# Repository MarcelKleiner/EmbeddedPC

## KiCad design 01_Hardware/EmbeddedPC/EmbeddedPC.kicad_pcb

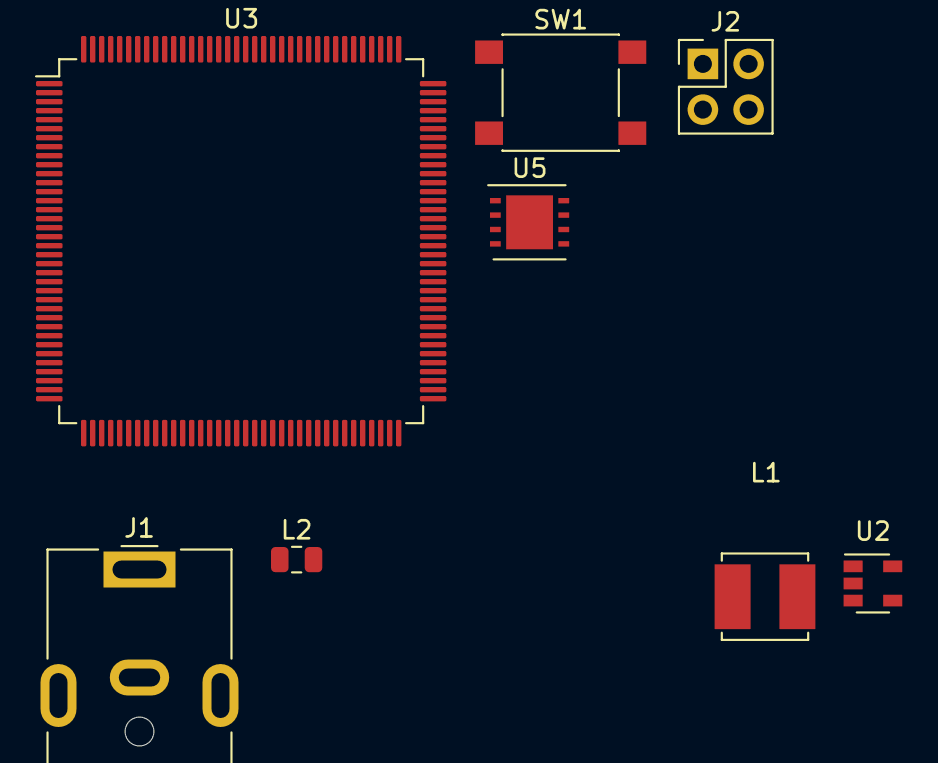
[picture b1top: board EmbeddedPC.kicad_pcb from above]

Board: 2 copper layers, 8 parts (0 on the bottom side), 4 nets, no tracks yet.

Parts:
J1: Jack-DC; BarrelJack_CUI_PJ-063AH_Horizontal
J2: RPG; PinHeader_2x02_P2.54mm_Vertical
L1: 47uH; L_4.8x4.8_H1.8
L2: 10uH; C_0805_2012Metric
SW1: SW_Push; SW_SPST_PTS645
U2: AP7370; SOT-23-5
U3: STM32H743ZITx; LQFP-144_20x20mm_P0.5mm
U5: TH58CVG3S0HRAIJ; WSON-8_4x4mm_P0.8mm

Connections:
+3V3: J2.1, U2.5, U3.17, U3.30, U3.33, U3.39, U3.52, U3.62, U3.72, U3.84, U3.95, U3.108, U3.121, U3.131, U3.144
GND: J1.2, J2.2, SW1.1, U2.2, U3.16, U3.31, U3.38, U3.51, U3.61, U3.83, U3.94, U3.107, U3.120, U3.130
unnamed: L2.2, U2.1
unnamed: SW1.2, U3.25

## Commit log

2021-03-30 Initial Commit Add Hardware Add Firmware
2021-04-02 update layout: - RAM - MCU - FLASH
2021-04-04 update hardware
2021-04-05 change fw configuration
